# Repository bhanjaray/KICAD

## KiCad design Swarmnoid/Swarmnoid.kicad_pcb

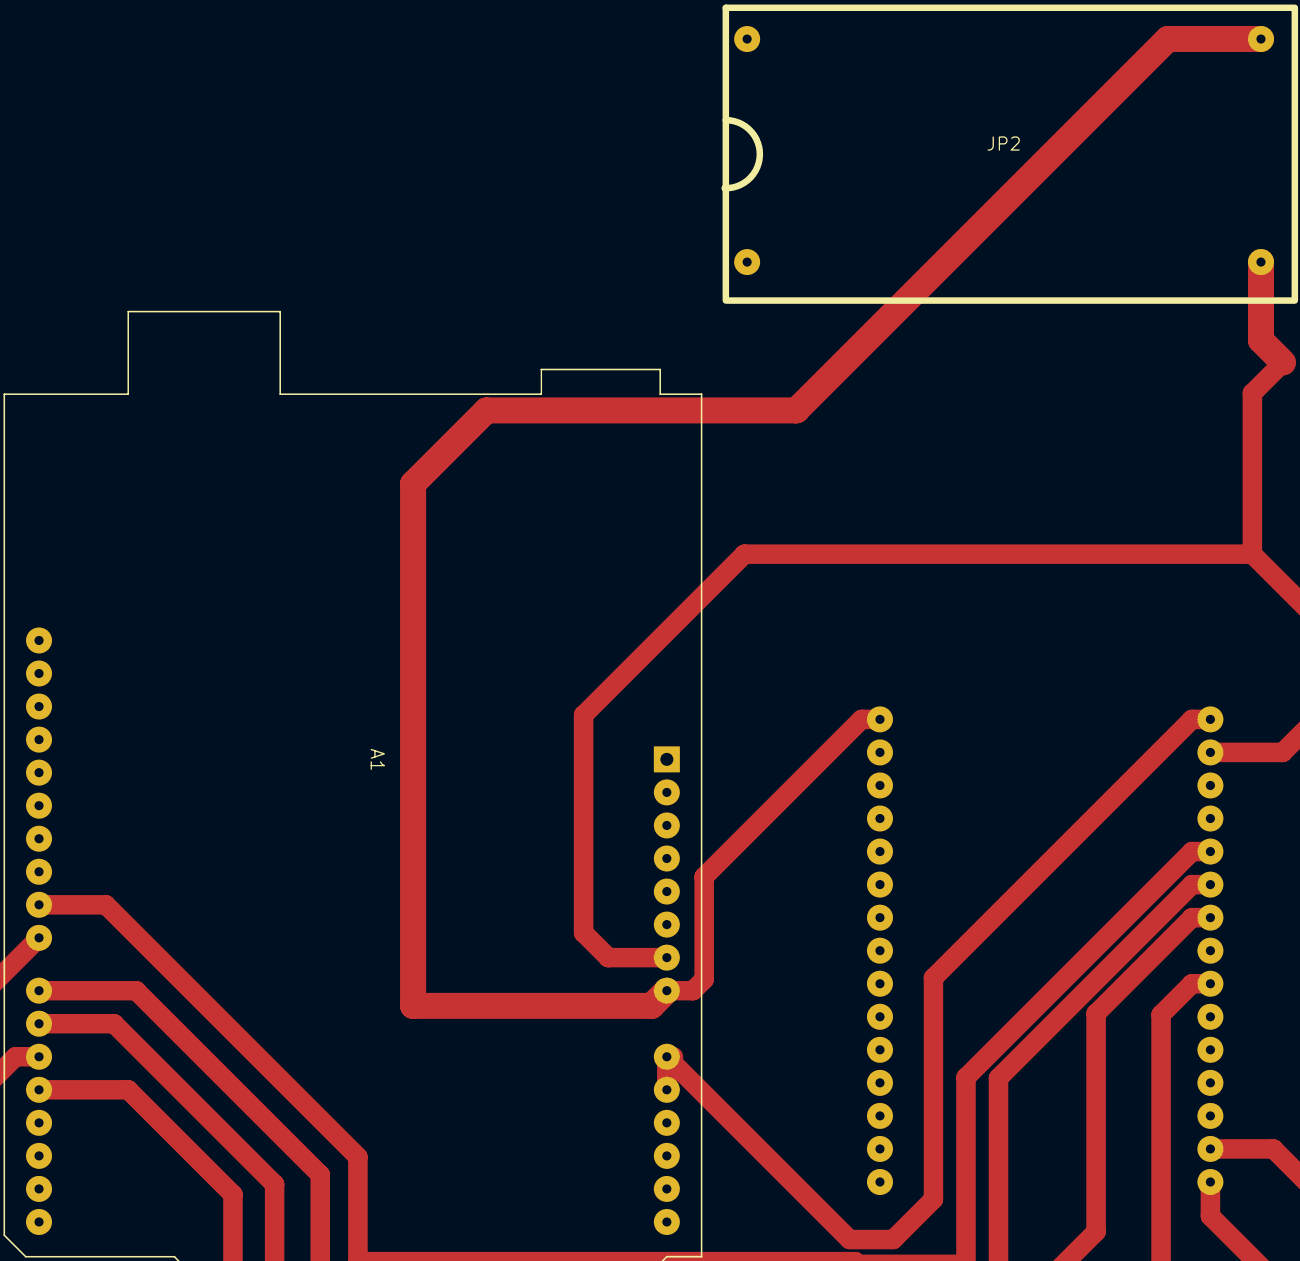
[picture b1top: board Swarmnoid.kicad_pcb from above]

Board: 2 copper layers, 3 parts (1 on the bottom side), 9 nets.

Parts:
A1: Arduino_UNO_R2; monster_motor_shield
JP1: esp32_module
JP2: Buck Converter

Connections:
unnamed: A1.9 (A0), A1.10 (A1), JP1.16 (3.3V)
unnamed: A1.19 (D4), JP1.24 (D18)
unnamed: A1.20 (D5), JP1.30 (D23)
unnamed: A1.21 (D6), JP1.22 (D17(TX2))
unnamed: A1.22 (D7), JP1.21 (D16(RX2))
unnamed: A1.23 (D8), JP1.29 (D22)
unnamed: A1.24 (D9), JP1.20 (D4)
unnamed: A1.8 (VIN), JP1.15 (VIN), JP2.3 (out+)
unnamed: A1.7 (GND), JP1.17 (GND), JP2.4 (out-)

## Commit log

2024-06-10 added kicad file
